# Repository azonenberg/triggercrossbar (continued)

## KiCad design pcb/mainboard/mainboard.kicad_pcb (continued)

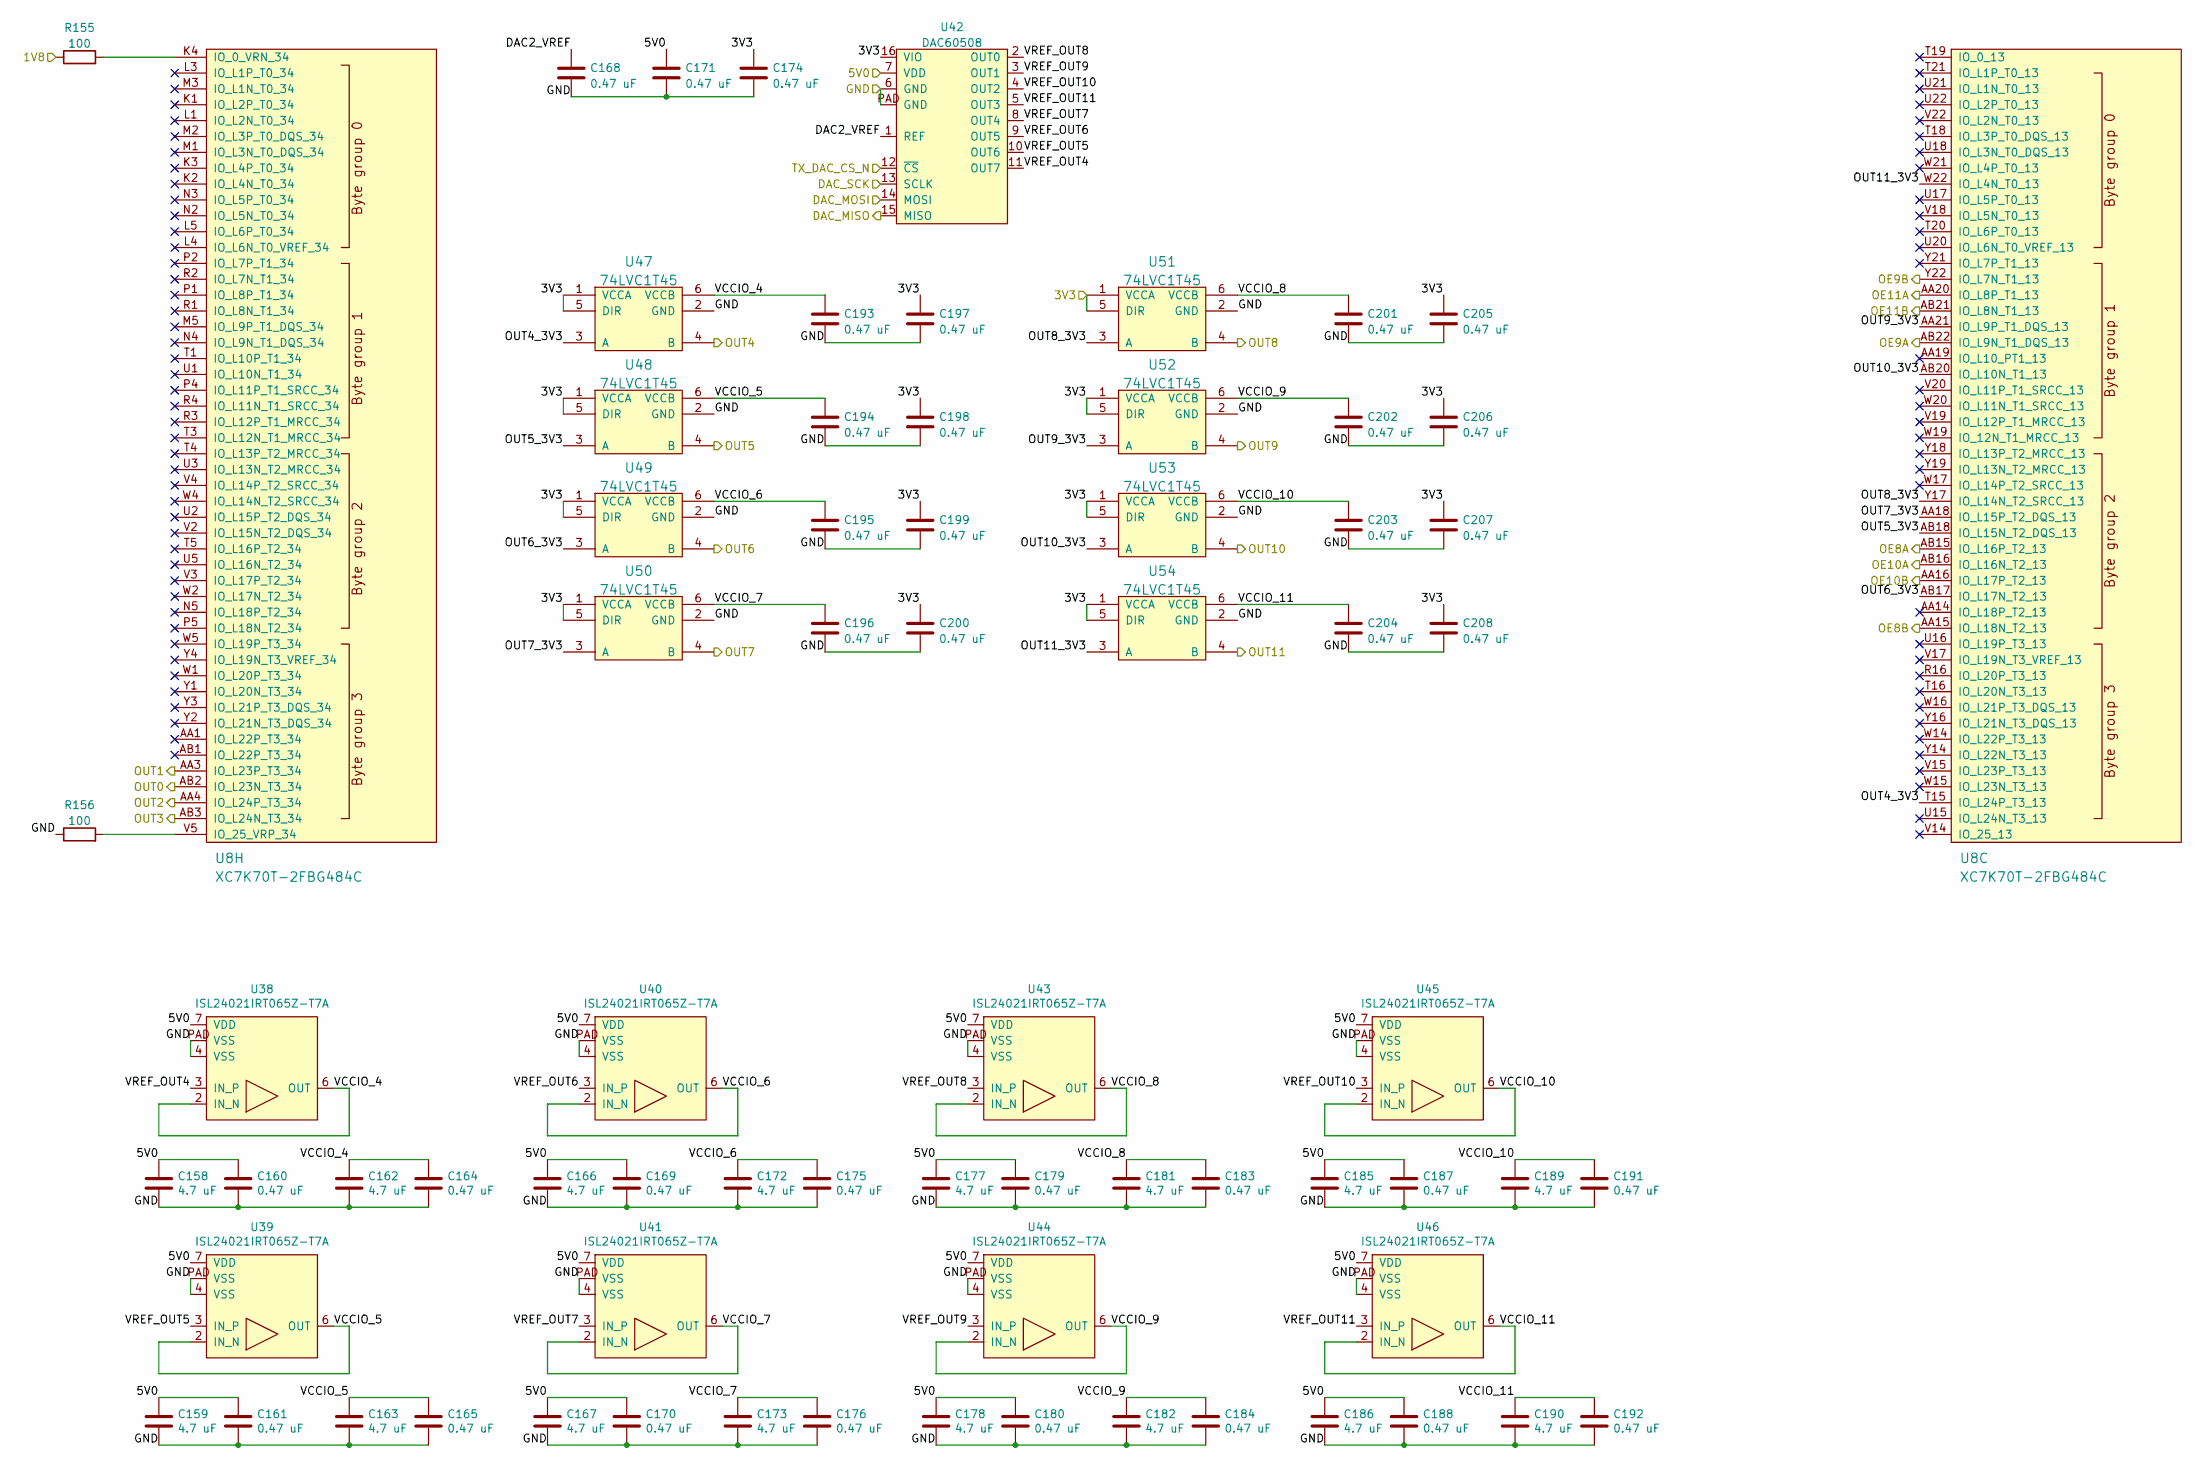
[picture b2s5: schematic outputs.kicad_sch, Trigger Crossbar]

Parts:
C158, C159, C162, C163, C166, C167, C172, C173, C177, C178, C181, C182, C185, C186, C189, C190: 4.7 uF; EIA_0603_CAP_NOSILK
C160, C161, C164, C165, C168, C169, C170, C171, C174, C175, C176, C179, C180, C183, C184, C187, C188, C191, C192, C193, C194, C195, C196, C197, C198, C199, C200, C201, C202, C203, C204, C205, C206, C207, C208: 0.47 uF; EIA_0402_CAP_NOSILK
R155, R156: 100; EIA_0402_RES_NOSILK
U8: XC7K70T-2FBG484C; BGA_484_22x22_FULLARRAY_1MM
U38, U39, U40, U41, U43, U44, U45, U46: ISL24021IRT065Z-T7A‎; DFN_8_0.65MM_3x3MM
U42: DAC60508; QFN_16_0.5MM_3x3MM
U47, U48, U49, U50, U51, U52, U53, U54: 74LVC1T45; DFN_6_0.5MM_1.6x1.6MM_TI_DPK

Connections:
/3V3: C174.1, C197.1, C198.1, C199.1, C200.1, C205.1, C206.1, C207.1, C208.1, U42.16 (VIO), U47.1 (VCCA), U47.5 (DIR), U48.1 (VCCA), U48.5 (DIR), U49.1 (VCCA), U49.5 (DIR), U50.1 (VCCA), U50.5 (DIR), U51.1 (VCCA), U51.5 (DIR), U52.1 (VCCA), U52.5 (DIR), U53.1 (VCCA), U53.5 (DIR), U54.1 (VCCA), U54.5 (DIR); also elsewhere on the board
/5V0: C158.1, C159.1, C160.1, C161.1, C166.1, C167.1, C169.1, C170.1, C171.1, C177.1, C178.1, C179.1, C180.1, C185.1, C186.1, C187.1, C188.1, U38.7 (VDD), U39.7 (VDD), U40.7 (VDD), U41.7 (VDD), U42.7 (VDD), U43.7 (VDD), U44.7 (VDD), U45.7 (VDD), U46.7 (VDD); also elsewhere on the board
/Connectors/OE8A: U8.AB15 (IO_L16P_T2_13); also elsewhere on the board
/Connectors/OE8B: U8.AA15 (IO_L18N_T2_13); also elsewhere on the board
/Connectors/OE9A: U8.AB22 (IO_L9N_T1_DQS_13); also elsewhere on the board
/Connectors/OE9B: U8.Y22 (IO_L7N_T1_13); also elsewhere on the board
/Connectors/OE10A: U8.AB16 (IO_L16N_T2_13); also elsewhere on the board
/Connectors/OE10B: U8.AA16 (IO_L17P_T2_13); also elsewhere on the board
/Connectors/OE11A: U8.AA20 (IO_L8P_T1_13); also elsewhere on the board
/Connectors/OE11B: U8.AB21 (IO_L8N_T1_13); also elsewhere on the board
/Connectors/OUT0: U8.AB2 (IO_L23N_T3_34); also elsewhere on the board
/Connectors/OUT1: U8.AA3 (IO_L23P_T3_34); also elsewhere on the board
/Connectors/OUT2: U8.AA4 (IO_L24P_T3_34); also elsewhere on the board
/Connectors/OUT3: U8.AB3 (IO_L24N_T3_34); also elsewhere on the board
/Connectors/OUT4: U47.4 (B); also elsewhere on the board
/Connectors/OUT5: U48.4 (B); also elsewhere on the board
/Connectors/OUT6: U49.4 (B); also elsewhere on the board
/Connectors/OUT7: U50.4 (B); also elsewhere on the board
/Connectors/OUT8: U51.4 (B); also elsewhere on the board
/Connectors/OUT9: U52.4 (B); also elsewhere on the board
/Connectors/OUT10: U53.4 (B); also elsewhere on the board
/Connectors/OUT11: U54.4 (B); also elsewhere on the board
/DAC_MISO: U42.15 (MISO); also elsewhere on the board
/DAC_MOSI: U42.14 (MOSI); also elsewhere on the board
/DAC_SCK: U42.13 (SCLK); also elsewhere on the board
/GND: C158.2, C159.2, C160.2, C161.2, C162.2, C163.2, C164.2, C165.2, C166.2, C167.2, C168.2, C169.2, C170.2, C171.2, C172.2, C173.2, C174.2, C175.2, C176.2, C177.2, C178.2, C179.2, C180.2, C181.2, C182.2, C183.2, C184.2, C185.2, C186.2, C187.2, C188.2, C189.2, C190.2, C191.2, C192.2, C193.2, C194.2, C195.2, C196.2, C197.2, C198.2, C199.2, C200.2, C201.2, C202.2, C203.2, C204.2, C205.2, C206.2, C207.2, C208.2, R156.1, U38.4 (VSS), U38.PAD (VSS), U39.4 (VSS), U39.PAD (VSS), U40.4 (VSS), U40.PAD (VSS), U41.4 (VSS), U41.PAD (VSS), U42.6 (GND), U42.PAD (GND), U43.4 (VSS), U43.PAD (VSS), U44.4 (VSS), U44.PAD (VSS), U45.4 (VSS), U45.PAD (VSS), U46.4 (VSS), U46.PAD (VSS), U47.2 (GND), U48.2 (GND), U49.2 (GND), U50.2 (GND), U51.2 (GND), U52.2 (GND), U53.2 (GND), U54.2 (GND); also elsewhere on the board
/Output/DAC2_VREF: C168.1, U42.1 (REF)
/Output/OUT4_3V3: U8.T15 (IO_L24P_T3_13), U47.3 (A)
/Output/OUT5_3V3: U8.AB18 (IO_L15N_T2_DQS_13), U48.3 (A)
/Output/OUT6_3V3: U8.AB17 (IO_L17N_T2_13), U49.3 (A)
/Output/OUT7_3V3: U8.AA18 (IO_L15P_T2_DQS_13), U50.3 (A)
/Output/OUT8_3V3: U8.Y17 (IO_L14N_T2_SRCC_13), U51.3 (A)
/Output/OUT9_3V3: U8.AA21 (IO_L9P_T1_DQS_13), U52.3 (A)
/Output/OUT10_3V3: U8.AB20 (IO_L10N_T1_13), U53.3 (A)
/Output/OUT11_3V3: U8.W22 (IO_L4N_T0_13), U54.3 (A)
/Output/VCCIO_4: C162.1, C164.1, C193.1, U38.2 (IN_N), U38.6 (OUT), U47.6 (VCCB)
/Output/VCCIO_5: C163.1, C165.1, C194.1, U39.2 (IN_N), U39.6 (OUT), U48.6 (VCCB)
/Output/VCCIO_6: C172.1, C175.1, C195.1, U40.2 (IN_N), U40.6 (OUT), U49.6 (VCCB)
/Output/VCCIO_7: C173.1, C176.1, C196.1, U41.2 (IN_N), U41.6 (OUT), U50.6 (VCCB)
/Output/VCCIO_8: C181.1, C183.1, C201.1, U43.2 (IN_N), U43.6 (OUT), U51.6 (VCCB)
/Output/VCCIO_9: C182.1, C184.1, C202.1, U44.2 (IN_N), U44.6 (OUT), U52.6 (VCCB)
/Output/VCCIO_10: C189.1, C191.1, C203.1, U45.2 (IN_N), U45.6 (OUT), U53.6 (VCCB)
/Output/VCCIO_11: C190.1, C192.1, C204.1, U46.2 (IN_N), U46.6 (OUT), U54.6 (VCCB)
/Output/VREF_OUT4: U38.3 (IN_P), U42.11 (OUT7)
/Output/VREF_OUT5: U39.3 (IN_P), U42.10 (OUT6)
/Output/VREF_OUT6: U40.3 (IN_P), U42.9 (OUT5)
/Output/VREF_OUT7: U41.3 (IN_P), U42.8 (OUT4)
/Output/VREF_OUT8: U42.2 (OUT0), U43.3 (IN_P)
/Output/VREF_OUT9: U42.3 (OUT1), U44.3 (IN_P)
/Output/VREF_OUT10: U42.4 (OUT2), U45.3 (IN_P)
/Output/VREF_OUT11: U42.5 (OUT3), U46.3 (IN_P)
/TX_DAC_CS_N: U42.12 (~CS); also elsewhere on the board
unnamed: R155.2, U8.K4 (IO_0_VRN_34)
unnamed: R156.2, U8.V5 (IO_25_VRP_34)

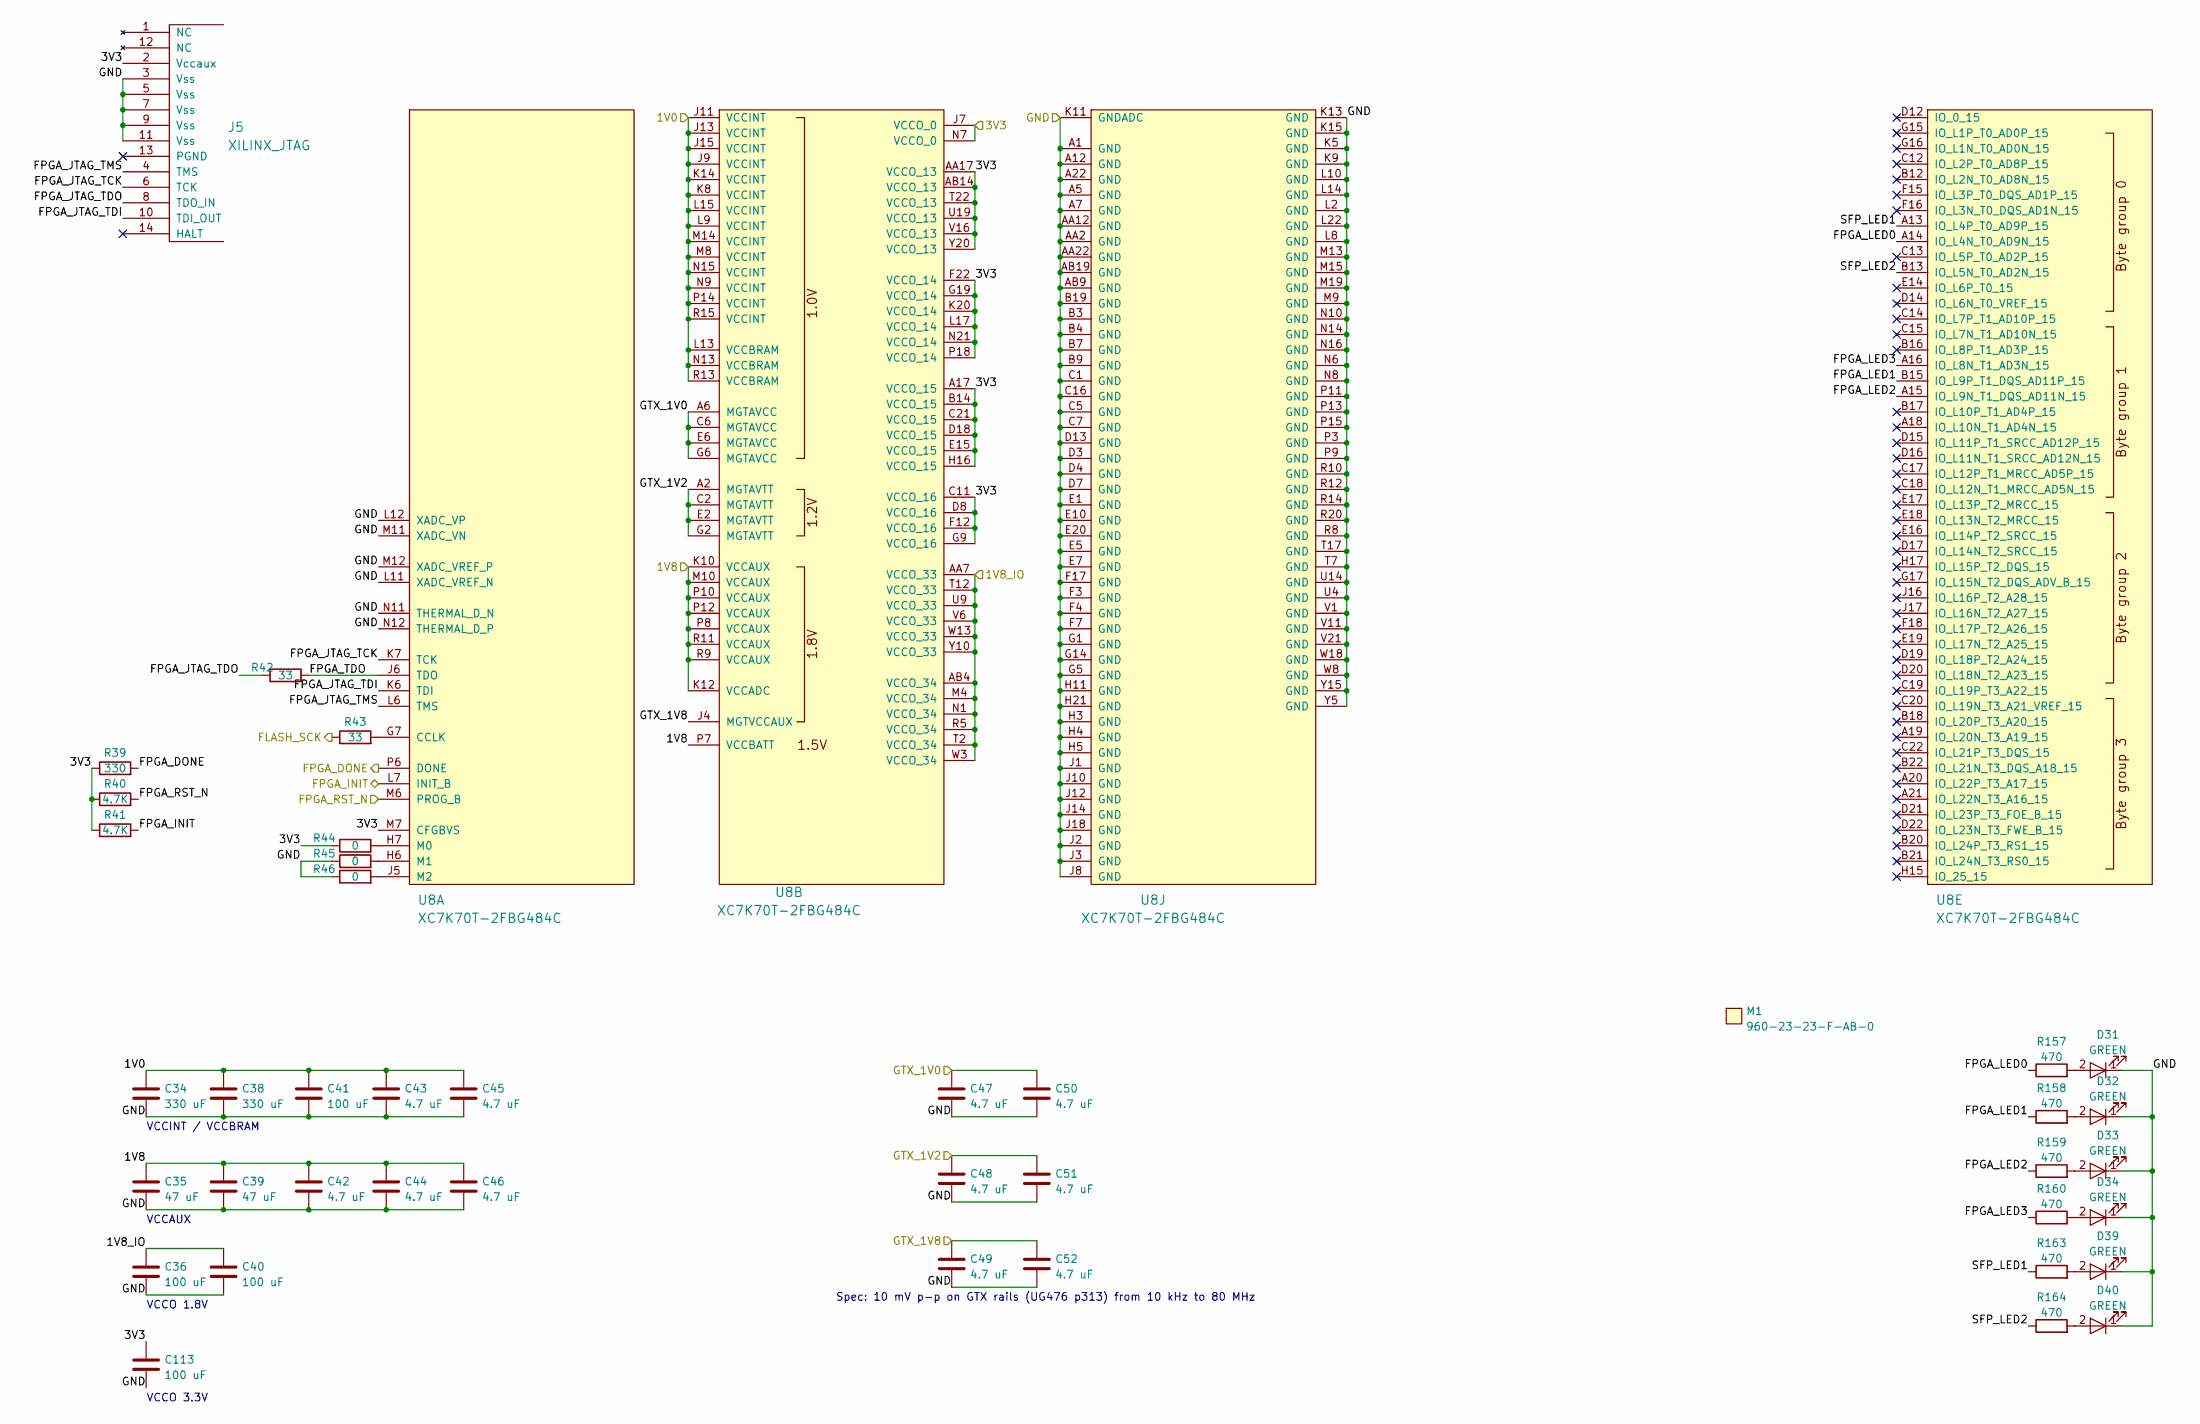
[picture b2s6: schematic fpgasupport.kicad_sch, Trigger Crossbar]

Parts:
C34, C38: 330 uF; EIA_1210_CAP_NOSILK
C35, C39: 47 uF; EIA_1210_CAP_NOSILK
C36, C40, C41: 100 uF; EIA_1206_CAP_NOSILK
C42, C43, C44, C45, C46, C47, C48, C49, C50, C51, C52: 4.7 uF; EIA_0603_CAP_NOSILK
C113: 100 uF; EIA_1210_CAP_NOSILK
D31, D32, D33, D34, D39, D40: GREEN; EIA_0603_LED
J5: XILINX_JTAG; XILINX_JTAG_PTH_MOLEX_0878311420
M1: 960-23-23-F-AB-0; HEATSINK_WAKEFIELDVETTE_960-23-23-F-AB-0
R39: 330; EIA_0402_RES_NOSILK
R40, R41: 4.7K; EIA_0402_RES_NOSILK
R42, R43: 33; EIA_0402_RES_NOSILK
R44, R45, R46: 0; EIA_0402_RES_NOSILK
R157, R158, R159, R160, R163, R164: 470; EIA_0402_RES_NOSILK
U8: XC7K70T-2FBG484C; BGA_484_22x22_FULLARRAY_1MM

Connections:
/1V2: C48.1, C51.1, U8.A2 (MGTAVTT), U8.C2 (MGTAVTT), U8.E2 (MGTAVTT), U8.G2 (MGTAVTT); also elsewhere on the board
/3V3: C113.1, J5.2 (Vccaux), R39.1, R40.1, R41.1, R44.1, U8.A17 (VCCO_15), U8.AA17 (VCCO_13), U8.AB14 (VCCO_13), U8.B14 (VCCO_15), U8.C11 (VCCO_16), U8.C21 (VCCO_15), U8.D8 (VCCO_16), U8.D18 (VCCO_15), U8.E15 (VCCO_15), U8.F12 (VCCO_16), U8.F22 (VCCO_14), U8.G9 (VCCO_16), U8.G19 (VCCO_14), U8.H16 (VCCO_15), U8.J7 (VCCO_0), U8.K20 (VCCO_14), U8.L17 (VCCO_14), U8.M7 (CFGBVS), U8.N7 (VCCO_0), U8.N21 (VCCO_14), U8.P18 (VCCO_14), U8.T22 (VCCO_13), U8.U19 (VCCO_13), U8.V16 (VCCO_13), U8.Y20 (VCCO_13); also elsewhere on the board
/FLASH_SCK: R43.1; also elsewhere on the board
/FPGA Support/1V0: C34.1, C38.1, C41.1, C43.1, C45.1, U8.J9 (VCCINT), U8.J11 (VCCINT), U8.J13 (VCCINT), U8.J15 (VCCINT), U8.K8 (VCCINT), U8.K14 (VCCINT), U8.L9 (VCCINT), U8.L13 (VCCBRAM), U8.L15 (VCCINT), U8.M8 (VCCINT), U8.M14 (VCCINT), U8.N9 (VCCINT), U8.N13 (VCCBRAM), U8.N15 (VCCINT), U8.P14 (VCCINT), U8.R13 (VCCBRAM), U8.R15 (VCCINT); also elsewhere on the board
/FPGA Support/FPGA_INIT: R41.2, U8.L7 (INIT_B); also elsewhere on the board
/FPGA Support/FPGA_JTAG_TCK: J5.6 (TCK), U8.K7 (TCK)
/FPGA Support/FPGA_JTAG_TDI: J5.10 (TDI_OUT), U8.K6 (TDI)
/FPGA Support/FPGA_JTAG_TDO: J5.8 (TDO_IN), R42.2
/FPGA Support/FPGA_JTAG_TMS: J5.4 (TMS), U8.L6 (TMS)
/FPGA Support/FPGA_LED0: R157.1, U8.A14 (IO_L4N_T0_AD9N_15)
/FPGA Support/FPGA_LED1: R158.1, U8.B15 (IO_L9P_T1_DQS_AD11P_15)
/FPGA Support/FPGA_LED2: R159.1, U8.A15 (IO_L9N_T1_DQS_AD11N_15)
/FPGA Support/FPGA_LED3: R160.1, U8.A16 (IO_L8N_T1_AD3N_15)
/FPGA Support/FPGA_RST_N: R40.2, U8.M6 (PROG_B); also elsewhere on the board
/FPGA Support/FPGA_TDO: R42.1, U8.J6 (TDO)
/FPGA Support/GTX_1V0: C47.1, C50.1, U8.A6 (MGTAVCC), U8.C6 (MGTAVCC), U8.E6 (MGTAVCC), U8.G6 (MGTAVCC); also elsewhere on the board
/FPGA Support/GTX_1V8: C49.1, C52.1, U8.J4 (MGTVCCAUX); also elsewhere on the board
/FPGA Support/SFP_LED1: R163.1, U8.A13 (IO_L4P_T0_AD9P_15)
/FPGA Support/SFP_LED2: R164.1, U8.B13 (IO_L5N_T0_AD2N_15)
/FPGA_DONE: R39.2, U8.P6 (DONE); also elsewhere on the board
/GND: C34.2, C35.2, C36.2, C38.2, C39.2, C40.2, C41.2, C42.2, C43.2, C44.2, C45.2, C46.2, C47.2, C48.2, C49.2, C50.2, C51.2, C52.2, C113.2, D31.1 (K), D32.1 (K), D33.1 (K), D34.1 (K), D39.1 (K), D40.1 (K), J5.3 (Vss), J5.5 (Vss), J5.7 (Vss), J5.9 (Vss), J5.11 (Vss), R45.1, R46.1, U8.A1 (GND), U8.A5 (GND), U8.A7 (GND), U8.A12 (GND), U8.A22 (GND), U8.AA2 (GND), U8.AA12 (GND), U8.AA22 (GND), U8.AB9 (GND), U8.AB19 (GND), U8.B3 (GND), U8.B4 (GND), U8.B7 (GND), U8.B9 (GND), U8.B19 (GND), U8.C1 (GND), U8.C5 (GND), U8.C7 (GND), U8.C16 (GND), U8.D3 (GND), U8.D4 (GND), U8.D7 (GND), U8.D13 (GND), U8.E1 (GND), U8.E5 (GND), U8.E7 (GND), U8.E10 (GND), U8.E20 (GND), U8.F3 (GND), U8.F4 (GND), U8.F7 (GND), U8.F17 (GND), U8.G1 (GND), U8.G5 (GND), U8.G14 (GND), U8.H3 (GND), U8.H4 (GND), U8.H5 (GND), U8.H11 (GND), U8.H21 (GND), U8.J1 (GND), U8.J2 (GND), U8.J3 (GND), U8.J8 (GND), U8.J10 (GND), U8.J12 (GND), U8.J14 (GND), U8.J18 (GND), U8.K5 (GND), U8.K9 (GND), U8.K11 (GNDADC), U8.K13 (GND), U8.K15 (GND), U8.L2 (GND), U8.L8 (GND), U8.L10 (GND), U8.L11 (XADC_VREF_N), U8.L12 (XADC_VP), U8.L14 (GND), U8.L22 (GND), U8.M9 (GND), U8.M11 (XADC_VN), U8.M12 (XADC_VREF_P), U8.M13 (GND), U8.M15 (GND), U8.M19 (GND), U8.N6 (GND), U8.N8 (GND), U8.N10 (GND), U8.N11 (THERMAL_D_N), U8.N12 (THERMAL_D_P), U8.N14 (GND), U8.N16 (GND), U8.P3 (GND), U8.P9 (GND), U8.P11 (GND), U8.P13 (GND), U8.P15 (GND), U8.R8 (GND), U8.R10 (GND), U8.R12 (GND), U8.R14 (GND), U8.R20 (GND), U8.T7 (GND), U8.T17 (GND), U8.U4 (GND), U8.U14 (GND), U8.V1 (GND), U8.V11 (GND), U8.V21 (GND), U8.W8 (GND), U8.W18 (GND), U8.Y5 (GND), U8.Y15 (GND); also elsewhere on the board
unnamed: D31.2 (A), R157.2
unnamed: D32.2 (A), R158.2
unnamed: D33.2 (A), R159.2
unnamed: D34.2 (A), R160.2
unnamed: D39.2 (A), R163.2
unnamed: D40.2 (A), R164.2
unnamed: R43.2, U8.G7 (CCLK)
unnamed: R44.2, U8.H7 (M0)
unnamed: R45.2, U8.H6 (M1)
unnamed: R46.2, U8.J5 (M2)

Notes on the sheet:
VCCO 1.8V
VCCAUX
Spec: 10 mV p-p on GTX rails (UG476 p313) from 10 kHz to 80 MHz
VCCO 3.3V
VCCINT / VCCBRAM

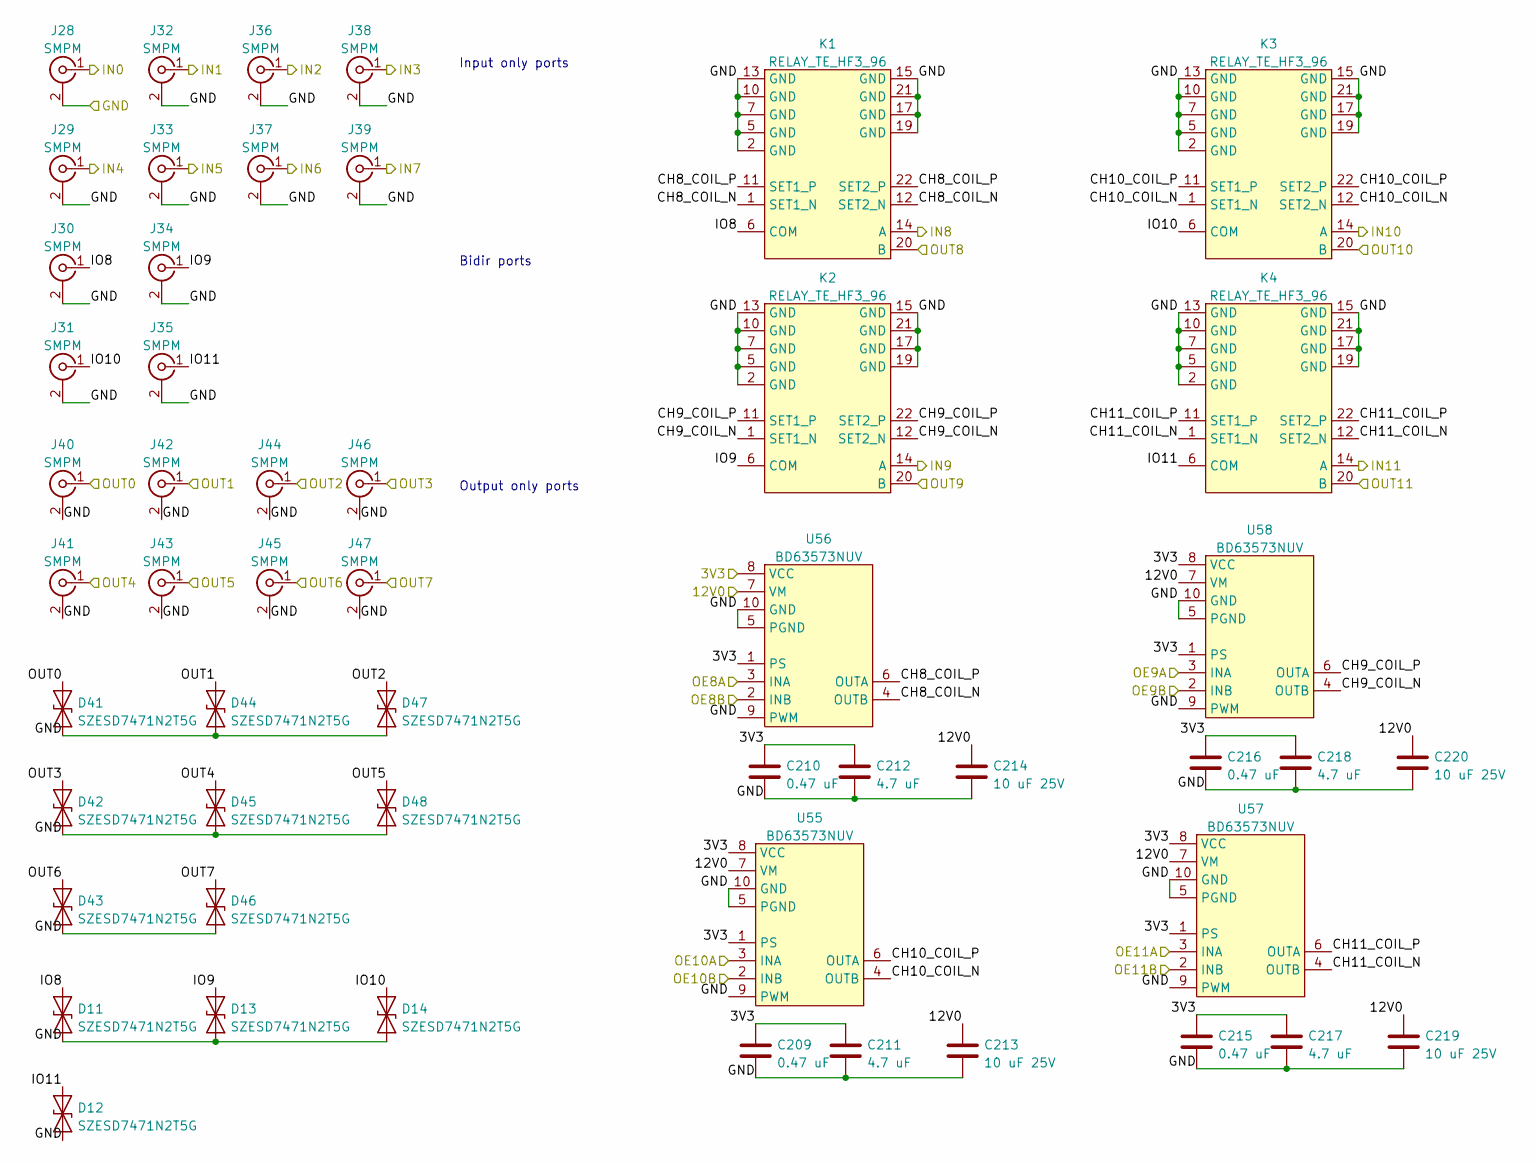
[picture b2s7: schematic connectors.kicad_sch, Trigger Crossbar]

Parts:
C209, C210, C215, C216: 0.47 uF; EIA_0402_CAP_NOSILK
C211, C212, C217, C218: 4.7 uF; EIA_0603_CAP_NOSILK
C213, C214, C219, C220: 10 uF 25V; EIA_1210_CAP_NOSILK
D11, D12, D13, D14, D41, D42, D43, D44, D45, D46, D47, D48: SZESD7471N2T5G; SOD882
J28, J29, J30, J31, J32, J33, J34, J35, J36, J37, J38, J39, J40, J41, J42, J43, J44, J45, J46, J47: SMPM; CONN_SMPM_AMPHENOL_C925-197J-51PT
K1, K2, K3, K4: RELAY_TE_HF3_96; RELAY_TE_HF3_2COIL_50OHM
U55, U56, U57, U58: BD63573NUV; DFN_10_0.5MM_3x3MM

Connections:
/3V3: C209.1, C210.1, C211.1, C212.1, C215.1, C216.1, C217.1, C218.1, U55.1 (PS), U55.8 (VCC), U56.1 (PS), U56.8 (VCC), U57.1 (PS), U57.8 (VCC), U58.1 (PS), U58.8 (VCC); also elsewhere on the board
/12V0: C213.1, C214.1, C219.1, C220.1, U55.7 (VM), U56.7 (VM), U57.7 (VM), U58.7 (VM); also elsewhere on the board
/Connectors/CH8_COIL_N: K1.1 (SET1_N), K1.12 (SET2_N), U56.4 (OUTB)
/Connectors/CH8_COIL_P: K1.11 (SET1_P), K1.22 (SET2_P), U56.6 (OUTA)
/Connectors/CH9_COIL_N: K2.1 (SET1_N), K2.12 (SET2_N), U58.4 (OUTB)
/Connectors/CH9_COIL_P: K2.11 (SET1_P), K2.22 (SET2_P), U58.6 (OUTA)
/Connectors/CH10_COIL_N: K3.1 (SET1_N), K3.12 (SET2_N), U55.4 (OUTB)
/Connectors/CH10_COIL_P: K3.11 (SET1_P), K3.22 (SET2_P), U55.6 (OUTA)
/Connectors/CH11_COIL_N: K4.1 (SET1_N), K4.12 (SET2_N), U57.4 (OUTB)
/Connectors/CH11_COIL_P: K4.11 (SET1_P), K4.22 (SET2_P), U57.6 (OUTA)
/Connectors/IN0: J28.1 (In); also elsewhere on the board
/Connectors/IN1: J32.1 (In); also elsewhere on the board
/Connectors/IN2: J36.1 (In); also elsewhere on the board
/Connectors/IN3: J38.1 (In); also elsewhere on the board
/Connectors/IN4: J29.1 (In); also elsewhere on the board
/Connectors/IN5: J33.1 (In); also elsewhere on the board
/Connectors/IN6: J37.1 (In); also elsewhere on the board
/Connectors/IN7: J39.1 (In); also elsewhere on the board
/Connectors/IN8: K1.14 (A); also elsewhere on the board
/Connectors/IN9: K2.14 (A); also elsewhere on the board
/Connectors/IN10: K3.14 (A); also elsewhere on the board
/Connectors/IN11: K4.14 (A); also elsewhere on the board
/Connectors/IO8: D11.2 (A2), J30.1 (In), K1.6 (COM)
/Connectors/IO9: D13.2 (A2), J34.1 (In), K2.6 (COM)
/Connectors/IO10: D14.2 (A2), J31.1 (In), K3.6 (COM)
/Connectors/IO11: D12.2 (A2), J35.1 (In), K4.6 (COM)
/Connectors/OE8A: U56.3 (INA); also elsewhere on the board
/Connectors/OE8B: U56.2 (INB); also elsewhere on the board
/Connectors/OE9A: U58.3 (INA); also elsewhere on the board
/Connectors/OE9B: U58.2 (INB); also elsewhere on the board
/Connectors/OE10A: U55.3 (INA); also elsewhere on the board
/Connectors/OE10B: U55.2 (INB); also elsewhere on the board
/Connectors/OE11A: U57.3 (INA); also elsewhere on the board
/Connectors/OE11B: U57.2 (INB); also elsewhere on the board
/Connectors/OUT0: D41.2 (A2), J40.1 (In); also elsewhere on the board
/Connectors/OUT1: D44.2 (A2), J42.1 (In); also elsewhere on the board
/Connectors/OUT2: D47.2 (A2), J44.1 (In); also elsewhere on the board
/Connectors/OUT3: D42.2 (A2), J46.1 (In); also elsewhere on the board
/Connectors/OUT4: D45.2 (A2), J41.1 (In); also elsewhere on the board
/Connectors/OUT5: D48.2 (A2), J43.1 (In); also elsewhere on the board
/Connectors/OUT6: D43.2 (A2), J45.1 (In); also elsewhere on the board
/Connectors/OUT7: D46.2 (A2), J47.1 (In); also elsewhere on the board
/Connectors/OUT8: K1.20 (B); also elsewhere on the board
/Connectors/OUT9: K2.20 (B); also elsewhere on the board
/Connectors/OUT10: K3.20 (B); also elsewhere on the board
/Connectors/OUT11: K4.20 (B); also elsewhere on the board
/GND: C209.2, C210.2, C211.2, C212.2, C213.2, C214.2, C215.2, C216.2, C217.2, C218.2, C219.2, C220.2, D11.1 (A1), D12.1 (A1), D13.1 (A1), D14.1 (A1), D41.1 (A1), D42.1 (A1), D43.1 (A1), D44.1 (A1), D45.1 (A1), D46.1 (A1), D47.1 (A1), D48.1 (A1), J28.2 (Ext), J29.2 (Ext), J30.2 (Ext), J31.2 (Ext), J32.2 (Ext), J33.2 (Ext), J34.2 (Ext), J35.2 (Ext), J36.2 (Ext), J37.2 (Ext), J38.2 (Ext), J39.2 (Ext), J40.2 (Ext), J41.2 (Ext), J42.2 (Ext), J43.2 (Ext), J44.2 (Ext), J45.2 (Ext), J46.2 (Ext), J47.2 (Ext), K1.2 (GND), K1.5 (GND), K1.7 (GND), K1.10 (GND), K1.13 (GND), K1.15 (GND), K1.17 (GND), K1.19 (GND), K1.21 (GND), K2.2 (GND), K2.5 (GND), K2.7 (GND), K2.10 (GND), K2.13 (GND), K2.15 (GND), K2.17 (GND), K2.19 (GND), K2.21 (GND), K3.2 (GND), K3.5 (GND), K3.7 (GND), K3.10 (GND), K3.13 (GND), K3.15 (GND), K3.17 (GND), K3.19 (GND), K3.21 (GND), K4.2 (GND), K4.5 (GND), K4.7 (GND), K4.10 (GND), K4.13 (GND), K4.15 (GND), K4.17 (GND), K4.19 (GND), K4.21 (GND), U55.5 (PGND), U55.9 (PWM), U55.10 (GND), U56.5 (PGND), U56.9 (PWM), U56.10 (GND), U57.5 (PGND), U57.9 (PWM), U57.10 (GND), U58.5 (PGND), U58.9 (PWM), U58.10 (GND); also elsewhere on the board

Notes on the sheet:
Bidir ports
Input only ports
Output only ports

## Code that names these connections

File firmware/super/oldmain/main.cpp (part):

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
void InitUART()
{
	//Initialize the UART for local console: 115.2 Kbps using PB6 for USART2 transmit and PB7 for USART2 receive
	//TODO: nice interface for enabling UART interrupts
	GPIOPin uart_tx(&GPIOB, 6, GPIOPin::MODE_PERIPHERAL, GPIOPin::SLEW_SLOW, 0);
	GPIOPin uart_rx(&GPIOB, 7, GPIOPin::MODE_PERIPHERAL, GPIOPin::SLEW_SLOW, 0);

	//Enable UART interrupts
	NVIC_EnableIRQ(28);
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{
	g_log("Initializing I2C interface\n");

	static GPIOPin i2c_scl(&GPIOA, 9, GPIOPin::MODE_PERIPHERAL, GPIOPin::SLEW_SLOW, 1, true);
	static GPIOPin i2c_sda(&GPIOA, 10, GPIOPin::MODE_PERIPHERAL, GPIOPin::SLEW_SLOW, 1, true);

	//I2C1 runs off our kernel clock (32 MHz)
	//Prescale by 8 to get 4 MHz
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	static GPIOPin fail_led(&GPIOH, 1, GPIOPin::MODE_OUTPUT, GPIOPin::SLEW_SLOW);
	static GPIOPin ok_led(&GPIOH, 0, GPIOPin::MODE_OUTPUT, GPIOPin::SLEW_SLOW);

	static GPIOPin fpga_done(&GPIOB, 11, GPIOPin::MODE_INPUT, 0, false);
	static GPIOPin mcu_rst_n(&GPIOA, 3, GPIOPin::MODE_OUTPUT, GPIOPin::SLEW_SLOW);
	static GPIOPin mcu_ready(&GPIOA, 0, GPIOPin::MODE_INPUT, 0, false);
	static GPIOPin fpga_rst_n(&GPIOA, 1, GPIOPin::MODE_OUTPUT, GPIOPin::SLEW_SLOW, 0, true);
	static GPIOPin fpga_init(&GPIOB, 12, GPIOPin::MODE_OUTPUT, 0, true);

	static GPIOPin pwr_button(&GPIOA, 12, GPIOPin::MODE_INPUT, 0, false);
	static GPIOPin rst_button(&GPIOA, 15, GPIOPin::MODE_INPUT, 0, false);
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	en_1v8 = 0;
	en_gtx_1v8 = 0;

	mcu_rst_n = 0;
	fpga_rst_n = 0;
	fpga_init = 0;
	fail_led = 0;
	ok_led = 0;

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	//Save the CS# pin
	g_spiCS = &spi_cs_n;

	//Set up IRQ7 for SPI CS# (PA4) change
	//Use EXTI4 as PA4 interrupt on falling edge
	//TODO: make a wrapper for this?
	volatile uint32_t* NVIC_ISER = (volatile uint32_t*)(0xe000e100);
	NVIC_ISER[0] |= 0x80;
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
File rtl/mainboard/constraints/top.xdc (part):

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set_property IOSTANDARD LVCMOS33 [get_ports rgmii_rxc]

set_property PACKAGE_PIN E4 [get_ports cdrtrig_n]
set_property PACKAGE_PIN D6 [get_ports gtx_refclk_156m25_p]
set_property PACKAGE_PIN F6 [get_ports gtx_refclk_200m_p]

set_property IOSTANDARD LVDS [get_ports clk_200mhz_p]
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set_property PACKAGE_PIN AB8 [get_ports {trig_in_p[1]}]
set_property PACKAGE_PIN V10 [get_ports {trig_in_p[0]}]

set_property PACKAGE_PIN G4 [get_ports sfp_rx_p]
set_property PACKAGE_PIN G21 [get_ports sfp_rx_los]
set_property IOSTANDARD LVCMOS33 [get_ports sfp_rx_los]
set_property IOSTANDARD LVCMOS33 [get_ports {sfp_led[1]}]
set_property IOSTANDARD LVCMOS33 [get_ports {sfp_led[0]}]
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set_property IOSTANDARD LVCMOS33 [get_ports rgmii_mdio]
set_property PACKAGE_PIN G10 [get_ports rgmii_rx_dv]
set_property IOSTANDARD LVCMOS33 [get_ports rgmii_rx_dv]
set_property PACKAGE_PIN B10 [get_ports rgmii_tx_clk]
set_property IOSTANDARD LVCMOS33 [get_ports rgmii_tx_clk]
set_property PACKAGE_PIN A10 [get_ports rgmii_tx_en]
set_property IOSTANDARD LVCMOS33 [get_ports rgmii_tx_en]
set_property IOSTANDARD LVCMOS33 [get_ports {rgmii_rxd[3]}]
set_property IOSTANDARD LVCMOS33 [get_ports {rgmii_rxd[2]}]
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set_property IOSTANDARD LVCMOS33 [get_ports frontpanel_mosi]
set_property IOSTANDARD LVCMOS33 [get_ports frontpanel_sck]
set_property PULLTYPE PULLUP [get_ports frontpanel_miso]
set_property PACKAGE_PIN N22 [get_ports frontpanel_cs_n]
set_property PACKAGE_PIN K21 [get_ports frontpanel_miso]
set_property PACKAGE_PIN L21 [get_ports frontpanel_mosi]
set_property PACKAGE_PIN K22 [get_ports frontpanel_sck]

set_property DRIVE 8 [get_ports frontpanel_cs_n]
set_property DRIVE 8 [get_ports frontpanel_mosi]
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set_property PACKAGE_PIN G18 [get_ports {flash_dq[2]}]
set_property PACKAGE_PIN H19 [get_ports {flash_dq[1]}]
set_property PACKAGE_PIN H18 [get_ports {flash_dq[0]}]
set_property PACKAGE_PIN L16 [get_ports flash_cs_n]
set_property IOSTANDARD LVCMOS33 [get_ports flash_cs_n]

set_property SLEW SLOW [get_ports {flash_dq[3]}]
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
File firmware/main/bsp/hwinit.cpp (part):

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
void BSP_InitUART()
{
	//Initialize the UART for local console: 115.2 Kbps using PA12 for UART4 transmit and PA11 for UART2 receive
	//TODO: nice interface for enabling UART interrupts
	static GPIOPin uart_tx(&GPIOA, 12, GPIOPin::MODE_PERIPHERAL, GPIOPin::SLEW_SLOW, 6);
	static GPIOPin uart_rx(&GPIOA, 11, GPIOPin::MODE_PERIPHERAL, GPIOPin::SLEW_SLOW, 6);

	//Enable the UART interrupt
	NVIC_EnableIRQ(52);
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	static GPIOPin mac_i2c_scl(&GPIOB, 8, GPIOPin::MODE_PERIPHERAL, GPIOPin::SLEW_SLOW, 6, true);
	static GPIOPin mac_i2c_sda(&GPIOB, 9, GPIOPin::MODE_PERIPHERAL, GPIOPin::SLEW_SLOW, 6, true);

	static GPIOPin sfp_i2c_scl(&GPIOF, 1, GPIOPin::MODE_PERIPHERAL, GPIOPin::SLEW_SLOW, 4, true);
	static GPIOPin sfp_i2c_sda(&GPIOF, 0, GPIOPin::MODE_PERIPHERAL, GPIOPin::SLEW_SLOW, 4, true);

	//Default kernel clock for I2C2 is is APB1 clock (68.75 MHz for our current config)
	//Prescale by 16 to get 4.29 MHz
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
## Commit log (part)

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2023-10-12 Initial README / design doc for intermediate bus converter
2023-10-16 Initial floorplan of IBC
2023-11-22 Initial skeleton firmware for IBC
2023-11-29 Updated IBC board for v0.2 with antialiasing filter, plane fix, and 5V standby rail
2023-12-15 Initial work on main PCB schematic
2023-12-17 Finished initial iteration of schematic, needs a verification pass to check for missing features then schematic review
2023-12-17 Calculated power monitor voltage divider
2023-12-18 Began assigning footprints
2023-12-19 Finished initial schematic review of trigger crossbar mainboard
2023-12-20 Continued initial layout work
2023-12-21 Initial placement of rear I/O connectors
2023-12-21 Grouped remaining components by subsystem, continued layout of IO area
2023-12-22 Hooked up most input pins
2023-12-23 Placed remainder of relays and drivers
2023-12-23 Tweaks to debug connectors, hooked up TX DAC
2023-12-23 Initial routing of supervisor MCU
2023-12-23 Initial layout of GTX_1V8 supply
2023-12-25 Continued layout, started plane fills. Everything routed except 1V8 regulator
2023-12-26 Updating file: mainboard.kicad_pcb with current fully routed design.
2023-12-26 Various small routing cleanups, silkscreen tweeks, and plane adjustments. DRC clean.
2023-12-26 Added some simulations
2023-12-30 Finished initial version of trigger crossbar mainboard
2024-01-03 Removed prepreg mentions from fab notes
2024-01-21 Updated fab notes with new stackup
2024-02-24 Updated to latest stm32-cpp
2024-02-24 Initial skeleton supervisor firmware copied from LATENTPINK
2024-02-24 Initial submodule integrations for MCU firmware
2024-02-24 Initial MCU firmware mostly copied from LATENTPINK
2024-02-24 Initial antikernel-ipcores submodule
2024-02-24 Initial vivado project skeleton
2024-02-25 Major progress on firmware and RTL bringup, entire output subsystem seems to be working fine
2024-02-26 Added soft power-on support
2024-02-26 Blink power LED if rails are all up, but FPGA is down
2024-02-26 Supervisor can now read temp sensor on IBC over I2C, but not yet talk to IBC firmware
2024-02-27 Initial 10G SFP+ link is operational, but not passing any packets yet since there's nothing on the other side of the MAC
2024-02-28 QSPI interface is now working. Ethernet is up and MCU is pingable, but seeing about 5% packet loss for no obvious reason.
2024-03-01 Initial SSH server integration, added GTX instance for front panel TX1 port
2024-03-02 Initial skeleton SCPI parser
2024-03-04 Firmware is now at minimum-viable status for basic trigger crossbar functionality (can control input and output levels, directions, and mux selectors via TCP SCPI)
2024-03-05 TX/RX pattern control now works over SCPI
2024-03-06 More work on SCPI interface for BERT TX ports
2024-03-09 Continued work on front panel
2024-03-09 Initial work on eye scan
2024-03-10 Refactoring of firmware to enable cleaner implementation of bathtub curve scans
2024-03-10 Updated front panel sch to use STM32L431 with more SRAM and SPI interfaces
2024-03-11 Finished initial front panel schematic and design review
2024-03-11 Fully routed front panel ready for layout review
2024-03-12 Final front panel design ready for manufacture
2024-03-13 Updated hopefully-final enclosure design
2024-03-13 PCB library updates
2024-03-15 Hopefully final rack chassis design
2024-03-16 Added CPLL configuration so we can hopefully eventually switch
2024-03-17 Added RX sub-rate support for eye patterns and bathtubs
2024-03-24 Initial skeleton front panel firmware
2024-03-24 Initial I/O expander support
2024-03-24 Initial low-level driver for e-ink display. Only supports single-pixel updates and the refresh is blocking for now.
2024-03-24 Lots of progress on display driver stuff
2024-03-25 IBC can now report its firmware version string over I2C to the supervisor
2024-03-26 Initial integration of supervisor with main MCU. Needs some work to use less blocking IO
2024-03-26 Power failure polling now uses same nonblocking sensor values
2024-03-27 Added FPGA bitstream version timestamp
2024-03-28 Remove some stale debug code
2024-03-28 FIxed incorrect fan RPM calculation. Added SPI registers to front panel for setting LEDs for bidirectional port state.
2024-03-28 LED snek now circles the front panel activity LEDs. Just need to implement pulse stretching in the FPGA now.
2024-03-31 Front panel display now refreshes every two hours, as well as after Ethernet link state changes. Base-T link speed on front panel is now correctly displayed.
2024-04-01 Improved handling of inbound 10GbE frames. Outbound 10G won't work without some more bitstream work.
2024-04-02 FPGA firmware version displayed no longer zero-prefixes day of month, to ensure consistency with MCU firmware version numbers
2024-04-03 ManagementTCPProtocol: generate proper random sequence numbers using STM32 crypto block, call base class methods for connection teardown
2024-04-03 Finished handling TCP retransmits
2024-04-03 Check for inbound Ethernet frames during long-running SCPI operations
2024-04-04 Initial implementation of SSH public key authentication works (software crypto)
2024-04-04 More work on public key login support, added "no ssh key" command
2024-04-09 Partial integration of new acceleration logic on FPGA
2024-04-09 SignExchangeHash: added FPGA acceleration
2024-04-09 DSA_BASE now integrates more functionality
2024-04-09 DeviceCryptoEngine: avoid reading back results we don't care about
2024-04-10 Initial restructuring of display code to support monochrome EPD panel
2024-04-10 Added IBC register for querying sense voltage, report that rather than internal output voltage on the front panel
2024-04-10 Initial state machine based refactoring of display driver
2024-04-11 Display subnet masks on front panel, link state is now on its own line
2024-04-12 Display message on front panel if we stop getting updates form the main MCU (via FPGA)
2024-04-12 Added CLI commands for configuring the IP address and forcing a screen refresh. Fixes #1.
2024-04-12 Allow configuration of SSH username
2024-04-14 Fixed some pop logic in ManagementRegisterInterface, fixed frequency of Timer1
2024-04-15 Bumped FPGA -> front panel SPI bus clock rate to 10 MHz
2024-04-16 Initial work on 8b10b decode trigger. Does block sync but no triggering yet
2024-04-19 Initial 64/66b CDR trigger decode work. Can decode 64/66b symbols in fabric but doesn't do anything with them yet.
2024-04-19 Upped CPU clock frequency to max (550 MHz) using external 25 MHz oscillator, vs ~512 using internal RC
2024-04-20 Front panel: converted UART to be a global variable rather than a pointer to a static (one less level of indirection for direct access)
2024-04-20 Converted g_logTimer to a global instead of a pointer
2024-04-20 Updated main CPU firmware to new UART model
2024-04-20 All firmware is now using new interrupt driven UART
2024-04-21 Updated Vivado project to 2023.2
2024-04-25 Initial NTP integration including front panel timestamping
2024-04-28 Updated ignores for newer kicad version
2024-04-28 Fixed incorrect key name used for bidir port drive levels
2024-04-29 Refactoring: changed QSPI bus to use "address" mode rather than "instruction" in order to support memory mapping in the future
2024-05-01 Initial bootloader for front panel. Supports basic CRC integrity checks and then starts application but doesn't have any SPI reflash capability yet
2024-05-02 PCB updates for kicad8
2024-05-04 Initial SFTP integration. Doesn't actually DFU yet, just throws away incoming data.
2024-05-05 Initial front panel DFU skeleton is progressing nicely. Can now jump to bootloader mode and return to application under SPI command, and query which mode we're in. No actual reflashing support yet.
2024-05-07 Initial front panel firmware updater is functional!
2024-05-08 Moved EthernetBus to a package
2024-05-09 Added "legacy read" and "legacy write" SPI instructions to avoid ambiguity as we start transitioning registers to APB. Moved some more headers to packages for better build/sim support
2024-05-10 MDIO controller is now using APB
2024-05-13 Front panel interface is now entirely controlled over APB
2024-05-13 Removed unnecessary synchronizers now that clk_crypt and management domain are the same clock
2024-05-14 Removed some commented-out dead code from ClockGeneration module
2024-05-15 10G MAC is now controlled over APB
2024-05-16 SERDES DRPs are now using APB
2024-05-17 1G Ethernet TX FIFO now uses APB
2024-05-18 Ethernet RX buffer is now connected over APB
2024-05-18 More peripherals are now directly memory mapped
2024-05-19 Memory mapped interrupt status register
2024-05-19 Converted status register back to 16 bits, no change in memory mapping behavior
2024-05-20 Removed debug ILAs
2024-05-20 Moved APB pipeline registers further from the root to improve timing
2024-05-20 Front panel SPI controller is now using memory mapped interface
2024-05-21 Began work on memory mapping DRP
2024-05-21 Finished converting all FPGA IO to new memory mapped model
2024-05-22 Front panel bootloader is now using common-embedded-platform
2024-05-25 Initial refactoring of main CPU firmware to use common platform
2024-05-26 Refactoring: moved a whole bunch of Ethernet-related init code to BSP rather than being in main app firmware, since bootloader will need it for SSH
2024-05-26 Added commands for application to reboot into DFU mode
2024-05-26 Front panel firmware now has bbram in common BSP
2024-05-26 Initial local serial console for bootloader
2024-05-30 Bootloader can now flash application binary and boot it successfully
2024-05-30 Updated PCB schematic with note about R134 errata
2024-05-31 Began work on FPGA DFU. Can erase and blank check flash and begin parsing bitstream, but doesn't actually write bitstream to flash yet.
2024-05-31 FPGA OTA flasher seems to be working? no multiboot support yet but that can come later. Fixes #7.
2024-05-31 Updated to latest staticnet
2024-06-02 Initial (single channel) CDR logic analyzer support
2024-06-08 Can now adjust trigger position on crossbar LA mode
2024-08-18 Updated submodules
2024-08-18 Continued work on new supervisor firmware, still need to handle buttons and input power failure
2024-08-18 Continued un-bitrotting firmware for latest libraries
2024-08-21 Can now SSH to bootloader although still using legacy indirect write path
2024-08-21 Bootloader for main MCU now builds under CMake
2024-08-21 Removed legacy makefile from bootloader
2024-08-21 Can now SSH to main application firmware, but fails to connect properly to front panel
2024-08-21 Properly handle build IDs during DFU
2024-08-22 Initial stats logging via ITM
2024-08-22 Log more sensor data by SWO
2024-08-22 Rearranged front panel firmware source to new directory structure
2024-08-22 Front panel firmware now builds under CMake
2024-08-22 Fixed include paths for front panel restructuring; added delays between back to back SPI transactions
2024-08-23 Removed dead methods
2024-09-15 Override APB_x_BUFCOUNT
2024-11-01 Initial work on task paradigm
2024-11-01 Removed MainLoopIteration now that everything is task based
2024-11-01 Task-ified supervisor
2024-11-02 Task-ified main firmware
2024-11-24 Initial work on IPv6 support
2024-12-24 Refactoring to use more CEP TCP/IP stuff
2024-12-24 MDIO and relay controller are now using linker script
2024-12-24 Removed DeviceCryptoEngine, now using AcceleratedCryptoEngine
2024-12-25 Removed ManagementPubkeyAuthenticator
2024-12-25 Use memory mapped writes for crossbar matrix config
2024-12-25 Changed QSPI clock to improve performance
2024-12-25 Removed dead SfrMemcpy function
2024-12-26 Serial ILA is now working with hard coded trigger config
2024-12-28 Now using L1 caches
2025-07-15 Initial AXI refactoring of Ethernet side
2025-07-16 Timing tweaks
2025-07-22 Moved some stuff out of tcmtext
2025-07-22 Flash interface IP is now quad capable
